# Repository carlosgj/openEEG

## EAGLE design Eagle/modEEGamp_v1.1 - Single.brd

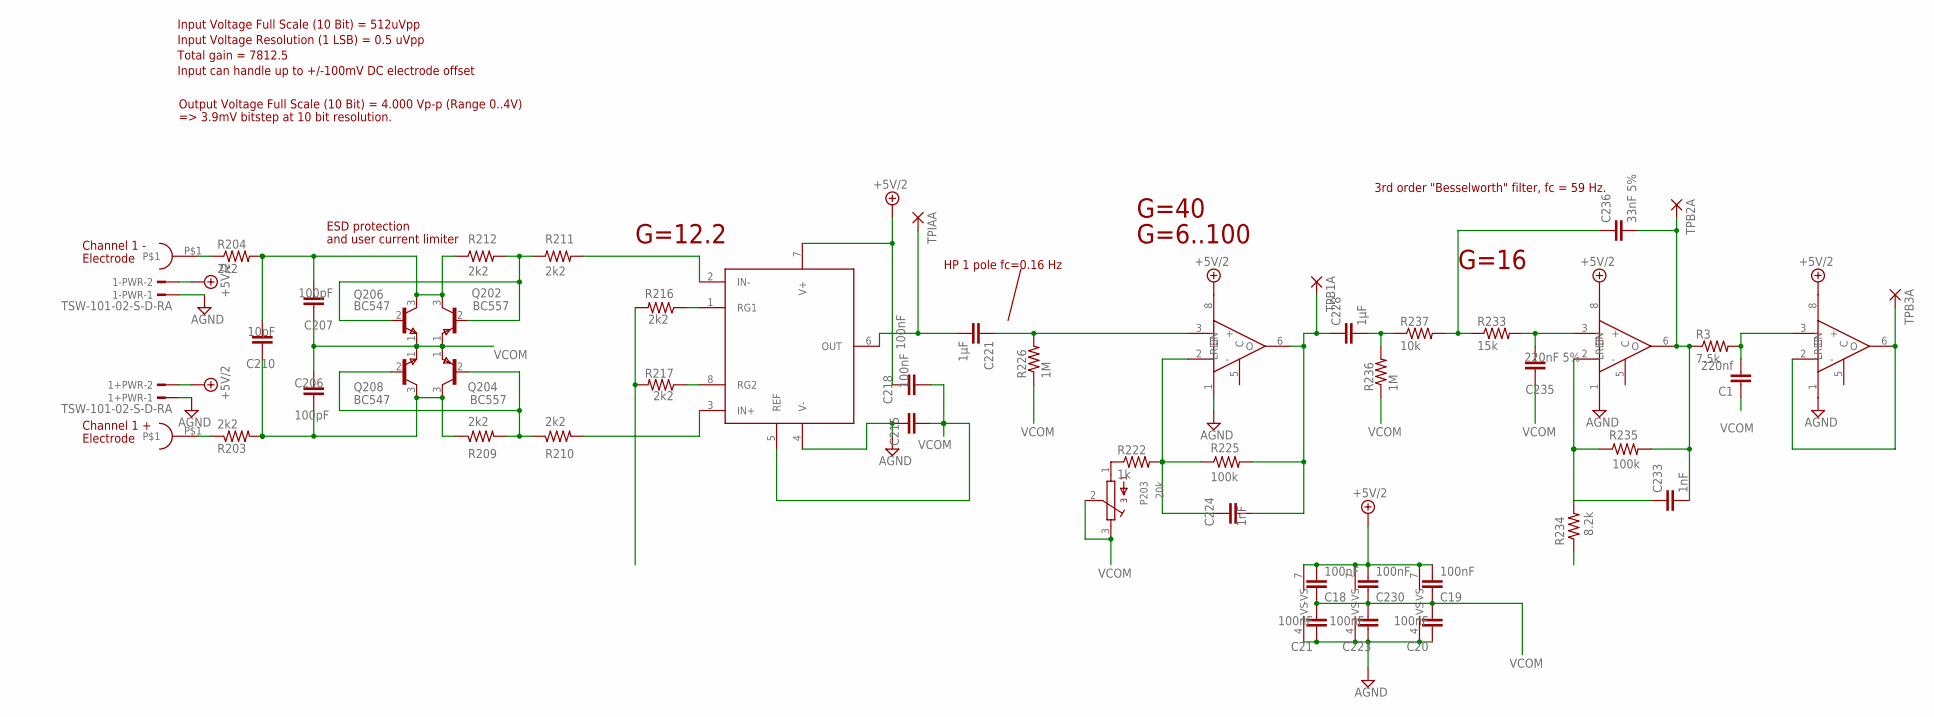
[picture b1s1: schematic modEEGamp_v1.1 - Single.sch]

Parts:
1+PWR, 1-PWR: TSW-101-02-S-D-RA
C1: 220nf; C1206
C1+, C1-: DIN42802
C18, C19, C20, C21, C215, C218, C223, C230: 100nF; C1206
C206, C207: 100pF; C1206
C210: 10pF; C1206
C221, C228: 1µF; C050-024X044
C224, C233: 1nF; C1206
C235: 220nF 5%; C1206
C236: 33nF 5%; C1206
P203: 20k; S64Y
Q202, Q204: BC557; TO92
Q206, Q208: BC547; TO92
R3: 7.5k; R1206
R203, R204, R209, R210, R211, R212, R216, R217: 2k2; R1206
R222: 1k; R1206
R225, R235: 100k; R1206
R226, R236: 1M; R1206
R233: 15k; R1206
R234: 8.2k; R1206
R237: 10k; R1206
TPB1A, TPB2A, TPB3A: 1,6/0,8
TPIAA: 1,6/0,8
U$1: INA217; DIL-08
U$2, U$3, U$16: AD8021; SOIC8

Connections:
+5V/2: 1+PWR.2, 1-PWR.2, C18.2, C19.2, C218.1, C230.2, U$1.7 (V+), U$2.7 (+VS), U$2.8 (EN), U$3.7 (+VS), U$3.8 (EN), U$16.7 (+VS), U$16.8 (EN)
ADIN0: TPB3A.1, U$16.2 (-), U$16.6 (O)
AGND: 1+PWR.1, 1-PWR.1, C20.1, C21.1, C215.1, C223.1, U$1.4 (V-), U$2.1 (LREF), U$2.4 (-VS), U$3.1 (LREF), U$3.4 (-VS), U$16.1 (LREF), U$16.4 (-VS)
unnamed: R216.1, U$1.1 (RG1)
unnamed: R217.1, U$1.8 (RG2)
unnamed: C233.2, C236.2, R3.1, R235.2, TPB2A.1, U$3.6 (O)
unnamed: C1-.P$1, R204.1
unnamed: C1.2, R3.2, U$16.3 (+)
unnamed: C1+.P$1, R203.1
unnamed: R216.2, R217.2
unnamed: R211.2, U$1.2 (IN-)
unnamed: C221.2, TPIAA.1, U$1.6 (OUT)
unnamed: R210.2, U$1.3 (IN+)
unnamed: C221.1, R226.2, U$2.3 (+)
unnamed: Q202.2 (B), Q206.2 (B), R211.1, R212.2
unnamed: C207.2, C210.2, Q202.3 (C), Q206.3 (C), R204.2, R212.1
unnamed: C224.1, R222.2, R225.1, U$2.2 (-)
unnamed: Q204.2 (B), Q208.2 (B), R209.2, R210.1
unnamed: P203.1, R222.1
unnamed: C224.2, C228.1, R225.2, TPB1A.1, U$2.6 (O)
unnamed: C206.1, C210.1, Q204.3 (C), Q208.3 (C), R203.2, R209.1
unnamed: C233.1, R234.2, R235.1, U$3.2 (-)
unnamed: C228.2, R236.2, R237.1
unnamed: C236.1, R233.1, R237.2
unnamed: C235.2, R233.2, U$3.3 (+)
VCOM: C1.1, C18.1, C19.1, C20.2, C21.2, C206.2, C207.1, C215.2, C218.2, C223.2, C230.1, C235.1, P203.2, P203.3, Q202.1 (E), Q204.1 (E), Q206.1 (E), Q208.1 (E), R226.1, R234.1, R236.1, U$1.5 (REF)

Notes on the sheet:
Electrode
Channel 1 -
Channel 1 +
Output Voltage Full Scale (10 Bit) = 4.000 Vp-p (Range 0..4V)
HP 1 pole fc=0.16 Hz
ESD protection
and user current limiter
G=12.2
G=16
G=40
G=6..100
Total gain = 7812.5
Input Voltage Resolution (1 LSB) = 0.5 uVpp
Input Voltage Full Scale (10 Bit) = 512uVpp
Input can handle up to +/-100mV DC electrode offset
3rd order "Besselworth" filter, fc = 59 Hz.
=> 3.9mV bitstep at 10 bit resolution.

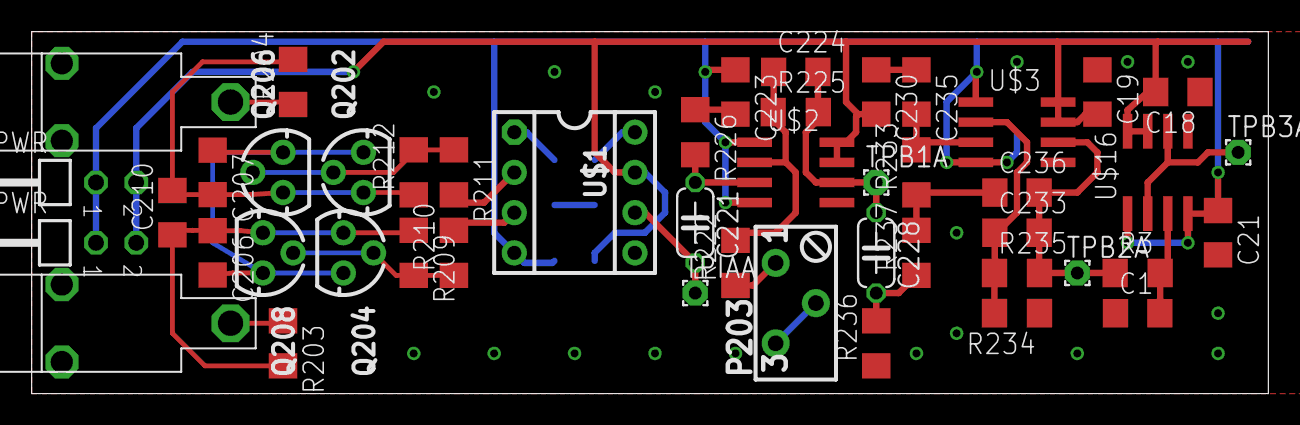
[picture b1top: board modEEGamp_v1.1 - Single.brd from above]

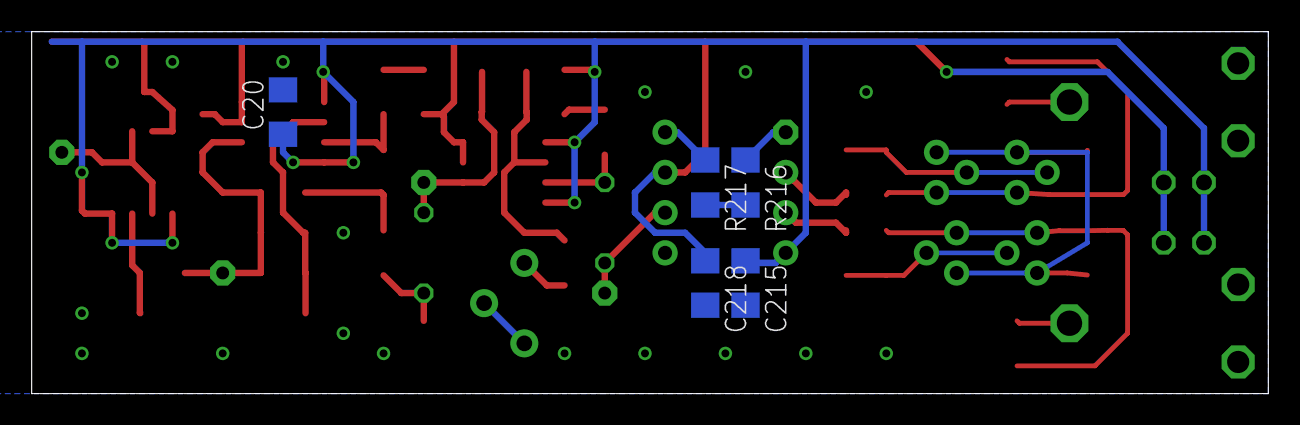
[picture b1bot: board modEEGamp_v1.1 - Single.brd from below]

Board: 2 copper layers, 78.1 x 22.9 mm, 52 parts (5 on the bottom side), 26 nets.

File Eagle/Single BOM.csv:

"Qty";"Value";"Device";"Package";"Parts";"Description";"";
"4";" ";"1,6/0,8";"1,6/0,8";"TPB1A, TPB2A, TPB3A, TPIAA";"THROUGH-HOLE PAD";"";
"2";"100k";"R-US_R1206";"R1206";"R225, R235";"RESISTOR, American symbol";"";
"8";"100nF";"C-EUC1206";"C1206";"C18, C19, C20, C21, C215, C218, C223, C230";"CAPACITOR, European symbol";"";
"2";"100pF";"C-EUC1206";"C1206";"C206, C207";"CAPACITOR, European symbol";"";
"1";"10k";"R-US_R1206";"R1206";"R237";"RESISTOR, American symbol";"";
"1";"10pF";"C-EUC1206";"C1206";"C210";"CAPACITOR, European symbol";"";
"1";"15k";"R-US_R1206";"R1206";"R233";"RESISTOR, American symbol";"";
"2";"1M";"R-US_R1206";"R1206";"R226, R236";"RESISTOR, American symbol";"";
"1";"1k";"R-US_R1206";"R1206";"R222";"RESISTOR, American symbol";"";
"2";"1nF";"C-EUC1206";"C1206";"C224, C233";"CAPACITOR, European symbol";"";
"2";"1µF";"C-EU050-024X044";"C050-024X044";"C221, C228";"CAPACITOR, European symbol";"";
"1";"20k";"S64Y";"S64Y";"P203";"";"";
"1";"220nF 5%";"C-EUC1206";"C1206";"C235";"CAPACITOR, European symbol";"";
"1";"220nf";"C-EUC1206";"C1206";"C1";"CAPACITOR, European symbol";"";
"8";"2k2";"R-US_R1206";"R1206";"R203, R204, R209, R210, R211, R212, R216, R217";"RESISTOR, American symbol";"";
"1";"33nF 5%";"C-EUC1206";"C1206";"C236";"CAPACITOR, European symbol";"";
"1";"7.5k";"R-US_R1206";"R1206";"R3";"RESISTOR, American symbol";"";
"1";"8.2k";"R-US_R1206";"R1206";"R234";"RESISTOR, American symbol";"";
"3";"AD8021";"AD8021";"SOIC8";"U$2, U$3, U$16";"";"";
"2";"BC547";"BC547";"TO92";"Q206, Q208";"";"";
"2";"BC557";"BC557";"TO92";"Q202, Q204";"";"";
"2";"DIN42802";"DIN42802";"DIN42802";"C1+, C1-";"";"";
"1";"INA217DW";"INA217DW";"DW_RPDSO-G16";"IC2";"Low-Noise, Low-Distortion INSTRUMENTATION AMPLIFIER Replacement for SSM2017";"";
"2";"TSW-101-02-S-D-RA";"TSW-101-02-S-D-RA";"TSW-101-02-S-D-RA";"1+PWR, 1-PWR";"THROUGH-HOLE .025" SQ POST HEADER";"";

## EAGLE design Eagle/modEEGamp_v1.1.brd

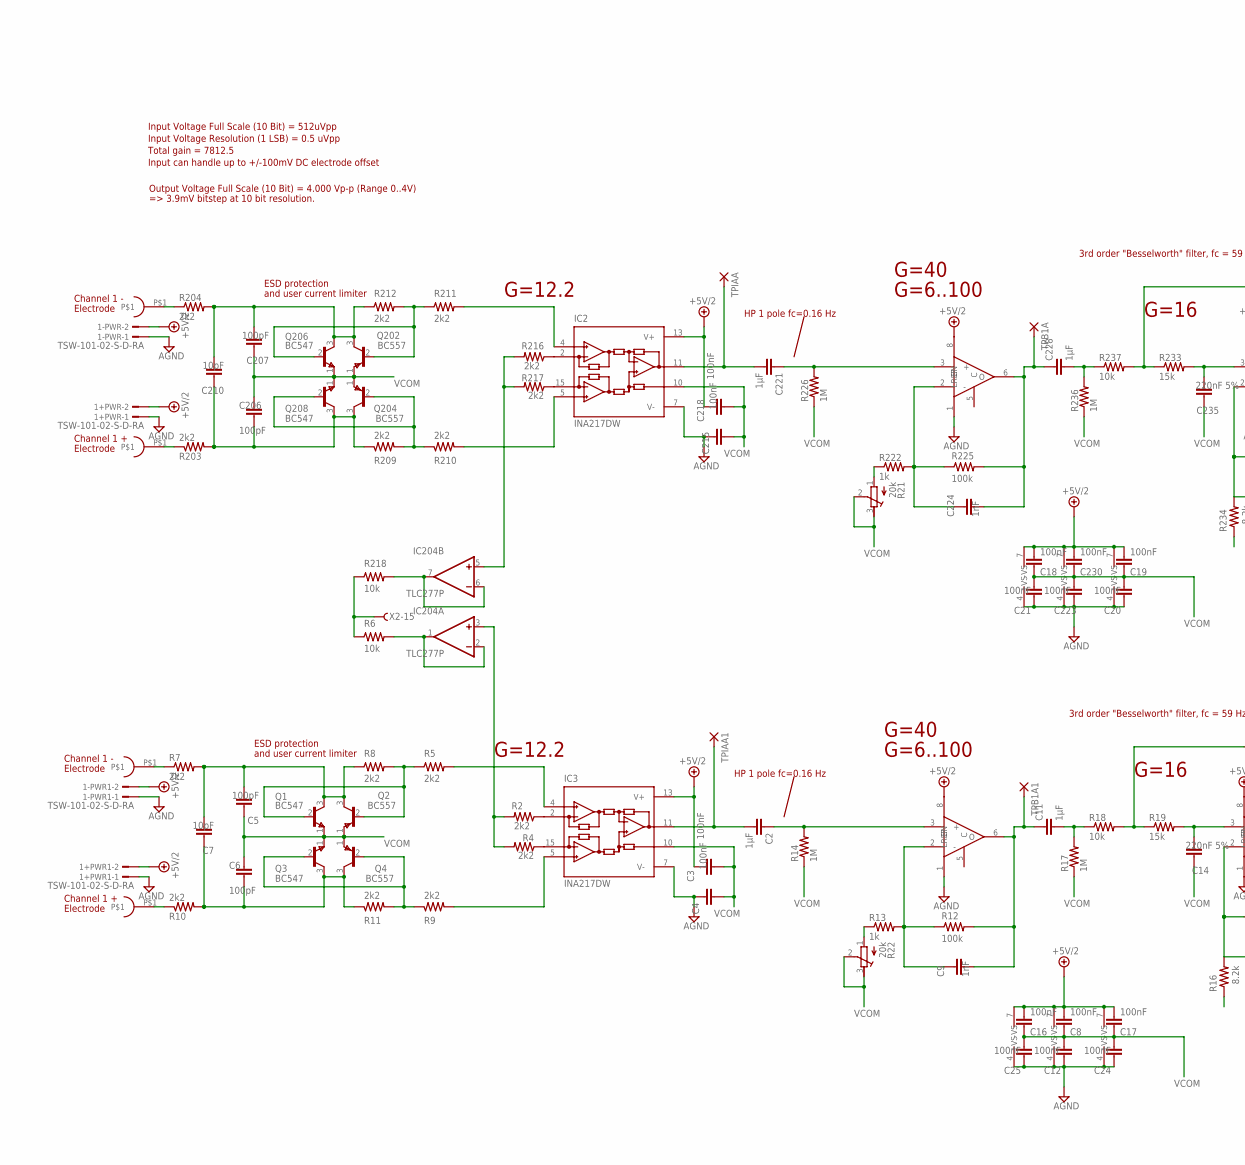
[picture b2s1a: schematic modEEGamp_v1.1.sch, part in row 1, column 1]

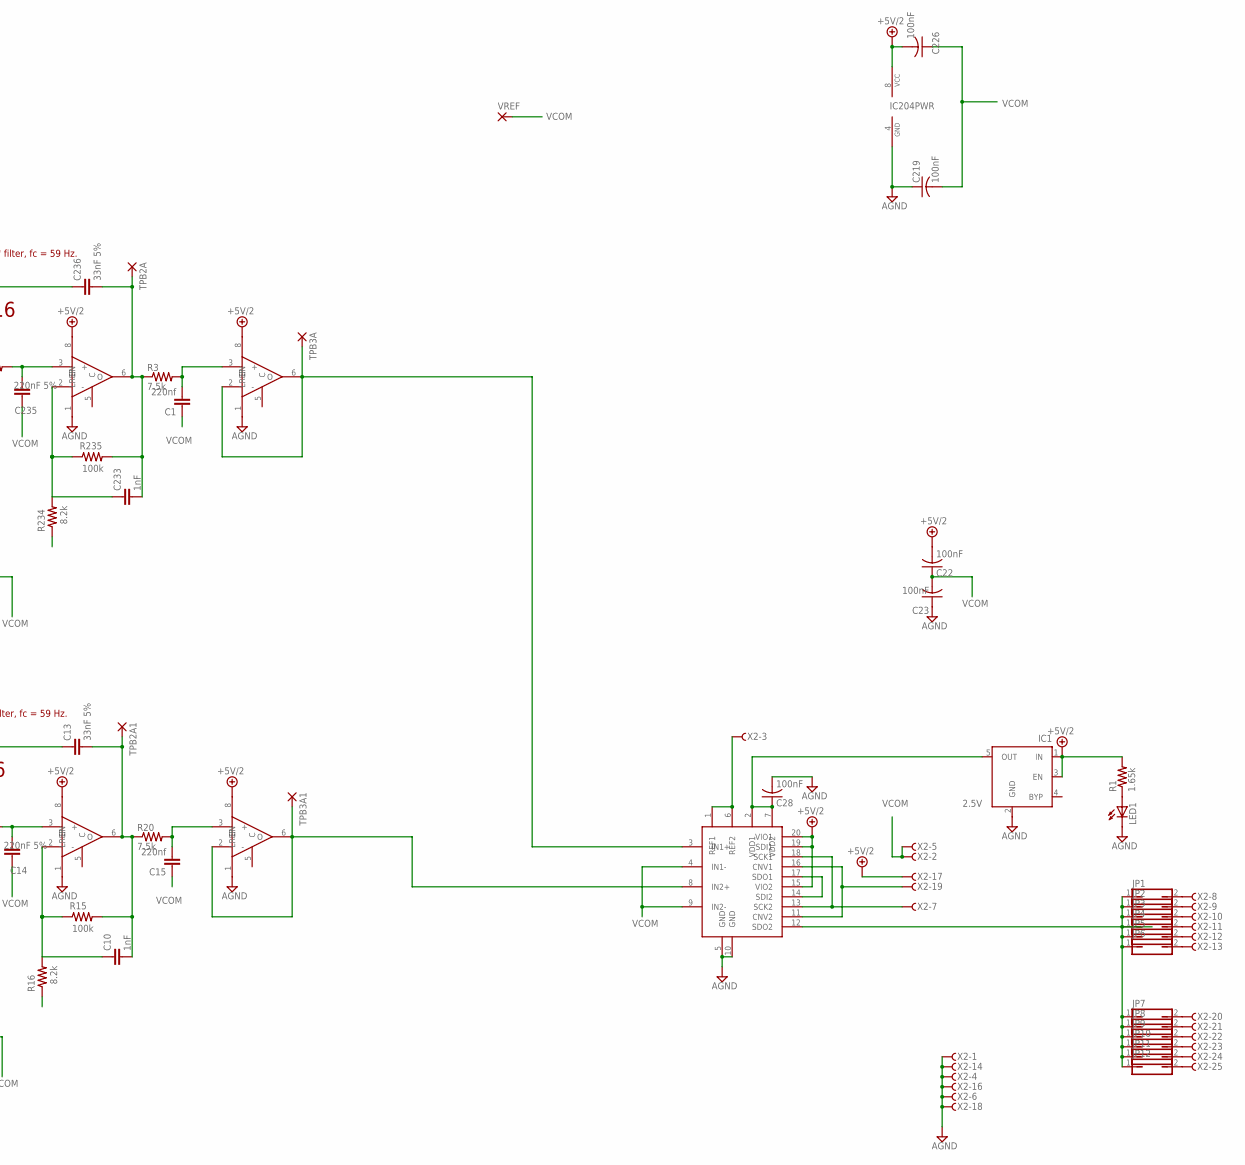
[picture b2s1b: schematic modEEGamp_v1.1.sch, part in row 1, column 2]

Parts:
1+PWR, 1+PWR1, 1-PWR, 1-PWR1: TSW-101-02-S-D-RA
C1, C15: 220nf; C1206
C1+, C1+1, C1-, C1-1: DIN42802
C2, C11, C221, C228: 1µF; C050-024X044
C3, C4, C8, C12, C16, C17, C18, C19, C20, C21, C22, C23, C24, C25, C28, C215, C218, C219, C223, C226, C230: 100nF; C1206
C5, C6, C206, C207: 100pF; C1206
C7, C210: 10pF; C1206
C9, C10, C224, C233: 1nF; C1206
C13, C236: 33nF 5%; C1206
C14, C235: 220nF 5%; C1206
IC1: 2.5V; SOT23-5
IC2, IC3: INA217DW; DW_RPDSO-G16
IC204: TLC277P; DIL-08
JP1, JP2, JP3, JP4, JP5, JP6, JP7, JP8, JP9, JP10, JP11, JP12: JP1Q; JP1
LED1: LED3MM
Q1, Q3, Q206, Q208: BC547; TO92
Q2, Q4, Q202, Q204: BC557; TO92
R1: 1.65k; R1206
R2, R4, R5, R7, R8, R9, R10, R11, R203, R204, R209, R210, R211, R212, R216, R217: 2k2; R1206
R3, R20: 7.5k; R1206
R6, R18, R218, R237: 10k; R1206
R12, R15, R225, R235: 100k; R1206
R13, R222: 1k; R1206
R14, R17, R226, R236: 1M; R1206
R16, R234: 8.2k; R1206
R19, R233: 15k; R1206
R21, R22: 20k; RTRIM3296W
TPB1A, TPB1A1, TPB2A, TPB2A1, TPB3A, TPB3A1: 1,6/0,8
TPIAA, TPIAA1: 1,6/0,8
U$1: AD7902; QSOP20
U$10, U$12, U$20, U$30, U$31, U$36: AD8021; SOIC8
VREF: 1,6/0,8
X2: F25HPS; F25HP

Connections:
+5V/2: 1+PWR.2, 1+PWR1.2, 1-PWR.2, 1-PWR1.2, C3.1, C8.2, C16.2, C17.2, C18.2, C19.2, C22.2, C218.1, C226.2, C230.2, IC1.1 (IN), IC1.3 (EN), IC2.13 (V+), IC3.13 (V+), IC204.8 (VCC), R1.2, U$1.15 (VIO2), U$1.19 (SDI1), U$1.20 (VIO1), U$10.7 (+VS), U$10.8 (EN), U$12.7 (+VS), U$12.8 (EN), U$20.7 (+VS), U$20.8 (EN), U$30.7 (+VS), U$30.8 (EN), U$31.7 (+VS), U$31.8 (EN), U$36.7 (+VS), U$36.8 (EN), X2.17
ADIN0: TPB3A.1, U$1.3 (IN1+), U$20.2 (-), U$20.6 (O)
ADIN1: TPB3A1.1, U$1.8 (IN2+), U$36.2 (-), U$36.6 (O)
AGND: 1+PWR.1, 1+PWR1.1, 1-PWR.1, 1-PWR1.1, C4.1, C12.1, C20.1, C21.1, C23.1, C24.1, C25.1, C28.2, C215.1, C219.1, C223.1, IC1.2 (GND), IC2.7 (V-), IC3.7 (V-), IC204.4 (GND), LED1.K (C), U$1.5 (GND), U$1.10 (GND), U$10.1 (LREF), U$10.4 (-VS), U$12.1 (LREF), U$12.4 (-VS), U$20.1 (LREF), U$20.4 (-VS), U$30.1 (LREF), U$30.4 (-VS), U$31.1 (LREF), U$31.4 (-VS), U$36.1 (LREF), U$36.4 (-VS), X2.1, X2.4, X2.6, X2.14, X2.16, X2.18
CNV: U$1.11 (CNV2), U$1.16 (CNV1), X2.19
unnamed: U$1.1 (REF1), U$1.6 (REF2), X2.3
unnamed: C28.1, IC1.5 (OUT), U$1.2 (VDD1), U$1.7 (VDD2)
unnamed: JP1.1, JP2.1, JP3.1, JP4.1, JP5.1, JP6.1, JP7.1, JP8.1, JP9.1, JP10.1, JP11.1, JP12.1, U$1.12 (SDO2)
unnamed: U$1.14 (SDI2), U$1.17 (SDO1)
unnamed: C1-.P$1, R204.1
unnamed: R13.1, R22.1 (A)
unnamed: C1+.P$1, R203.1
unnamed: R21.1 (A), R222.1
unnamed: LED1.A, R1.1
unnamed: JP1.2, X2.8
unnamed: JP2.2, X2.9
unnamed: IC204.5 (+IN), R216.2, R217.2
unnamed: C233.2, C236.2, R3.1, R235.2, TPB2A.1, U$12.6 (O)
unnamed: IC2.2 (RG1), R216.1
unnamed: C1.2, R3.2, U$20.3 (+)
unnamed: IC204.3 (+IN), R2.2, R4.2
unnamed: C2.2, IC3.11 (OUT), TPIAA1.1
unnamed: IC3.4 (-IN), R5.2
unnamed: IC3.5 (+IN), R9.2
unnamed: IC2.15 (RG2), R217.1
unnamed: IC2.4 (-IN), R211.2
unnamed: Q1.2 (B), Q2.2 (B), R5.1, R8.2
unnamed: C5.2, C7.2, Q1.3 (C), Q2.3 (C), R7.2, R8.1
unnamed: Q3.2 (B), Q4.2 (B), R9.1, R11.2
unnamed: C221.2, IC2.11 (OUT), TPIAA.1
unnamed: C6.1, C7.1, Q3.3 (C), Q4.3 (C), R10.2, R11.1
unnamed: IC2.5 (+IN), R210.2
unnamed: C221.1, R226.2, U$10.3 (+)
unnamed: Q202.2 (B), Q206.2 (B), R211.1, R212.2
unnamed: C1-1.P$1, R7.1
unnamed: C1+1.P$1, R10.1
unnamed: C207.2, C210.2, Q202.3 (C), Q206.3 (C), R204.2, R212.1
unnamed: C2.1, R14.2, U$30.3 (+)
unnamed: C9.1, R12.1, R13.2, U$30.2 (-)
unnamed: IC204.1 (OUT), IC204.2 (-IN), R6.2
unnamed: JP3.2, X2.10
unnamed: C9.2, C11.1, R12.2, TPB1A1.1, U$30.6 (O)
unnamed: C224.1, R222.2, R225.1, U$10.2 (-)
unnamed: Q204.2 (B), Q208.2 (B), R209.2, R210.1
unnamed: JP4.2, X2.11
unnamed: C13.1, R18.2, R19.1
unnamed: C224.2, C228.1, R225.2, TPB1A.1, U$10.6 (O)
unnamed: C206.1, C210.1, Q204.3 (C), Q208.3 (C), R203.2, R209.1
unnamed: C14.2, R19.2, U$31.3 (+)
unnamed: C11.2, R17.2, R18.1
unnamed: C10.1, R15.1, R16.2, U$31.2 (-)
unnamed: IC3.2 (RG1), R2.1
unnamed: IC3.15 (RG2), R4.1
unnamed: C233.1, R234.2, R235.1, U$12.2 (-)
unnamed: C228.2, R236.2, R237.1
unnamed: C236.1, R233.1, R237.2
unnamed: IC204.6 (-IN), IC204.7 (OUT), R218.2
unnamed: C10.2, C13.2, R15.2, R20.1, TPB2A1.1, U$31.6 (O)
unnamed: C15.2, R20.2, U$36.3 (+)
unnamed: JP5.2, X2.12
unnamed: JP6.2, X2.13
unnamed: C235.2, R233.2, U$12.3 (+)
unnamed: JP7.2, X2.20
unnamed: JP8.2, X2.21
unnamed: JP9.2, X2.22
unnamed: JP10.2, X2.23
unnamed: JP11.2, X2.24
unnamed: JP12.2, X2.25
unnamed: R6.1, R218.1, X2.15
SCK: U$1.13 (SCK2), U$1.18 (SCK1), X2.7
VCOM: C1.1, C3.2, C4.2, C5.1, C6.2, C8.1, C12.2, C14.1, C15.1, C16.1, C17.1, C18.1, C19.1, C20.2, C21.2, C22.1, C23.2, C24.2, C25.2, C206.2, C207.1, C215.2, C218.2, C219.2, C223.2, C226.1, C230.1, C235.1, IC2.10 (REF), IC3.10 (REF), Q1.1 (E), Q2.1 (E), Q3.1 (E), Q4.1 (E), Q202.1 (E), Q204.1 (E), Q206.1 (E), Q208.1 (E), R14.1, R16.1, R17.1, R21.2 (S), R21.3 (E), R22.2 (S), R22.3 (E), R226.1, R234.1, R236.1, U$1.4 (IN1-), U$1.9 (IN2-), VREF.1, X2.2, X2.5

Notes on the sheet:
Electrode
Channel 1 -
Channel 1 +
Output Voltage Full Scale (10 Bit) = 4.000 Vp-p (Range 0..4V)
HP 1 pole fc=0.16 Hz
ESD protection
and user current limiter
G=12.2
G=16
G=40
G=6..100
Total gain = 7812.5
Input Voltage Resolution (1 LSB) = 0.5 uVpp
Input Voltage Full Scale (10 Bit) = 512uVpp
Input can handle up to +/-100mV DC electrode offset
3rd order "Besselworth" filter, fc = 59 Hz.
=> 3.9mV bitstep at 10 bit resolution.

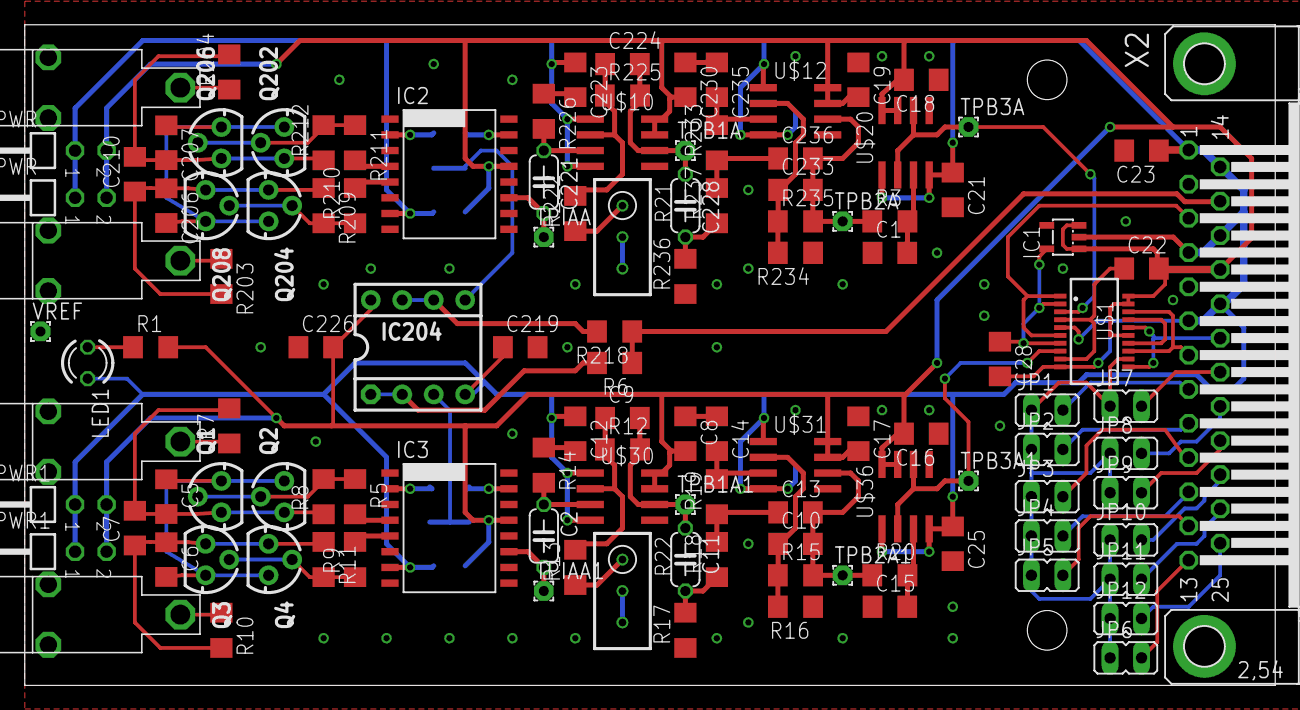
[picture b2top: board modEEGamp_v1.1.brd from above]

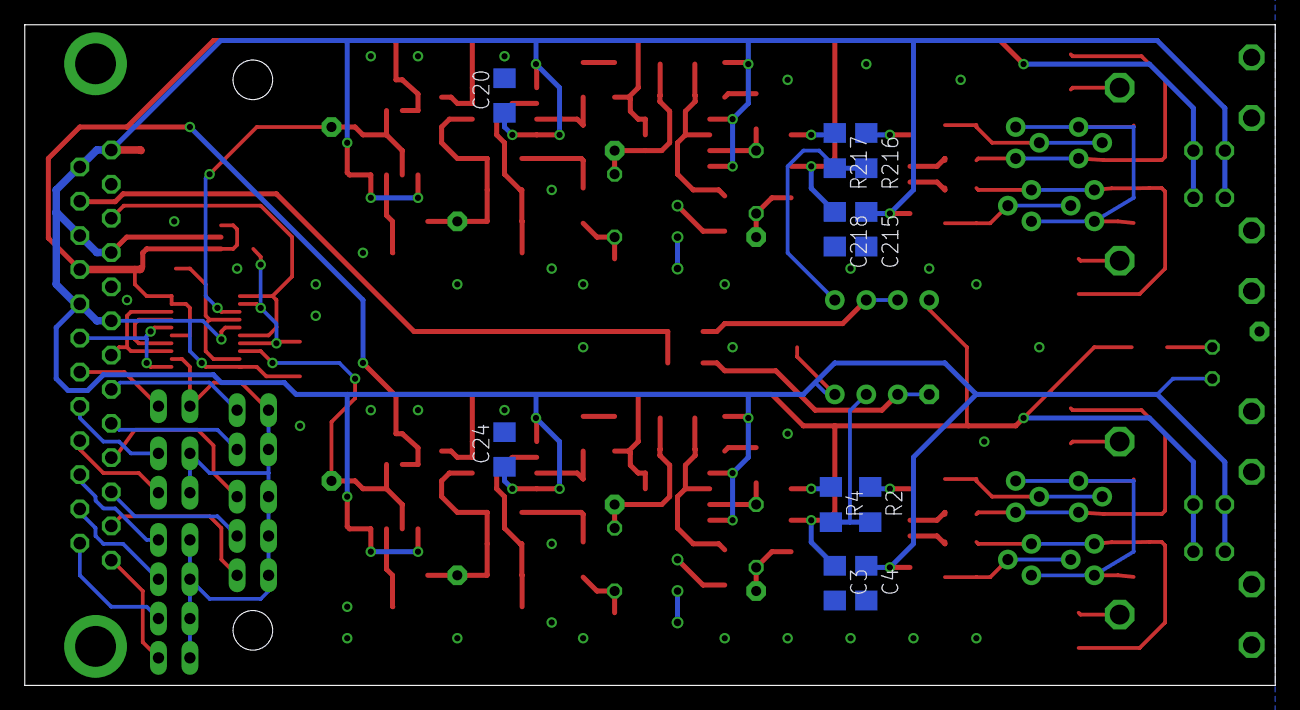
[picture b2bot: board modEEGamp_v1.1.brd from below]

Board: 2 copper layers, 101.0 x 53.3 mm, 130 parts (10 on the bottom side), 71 nets.

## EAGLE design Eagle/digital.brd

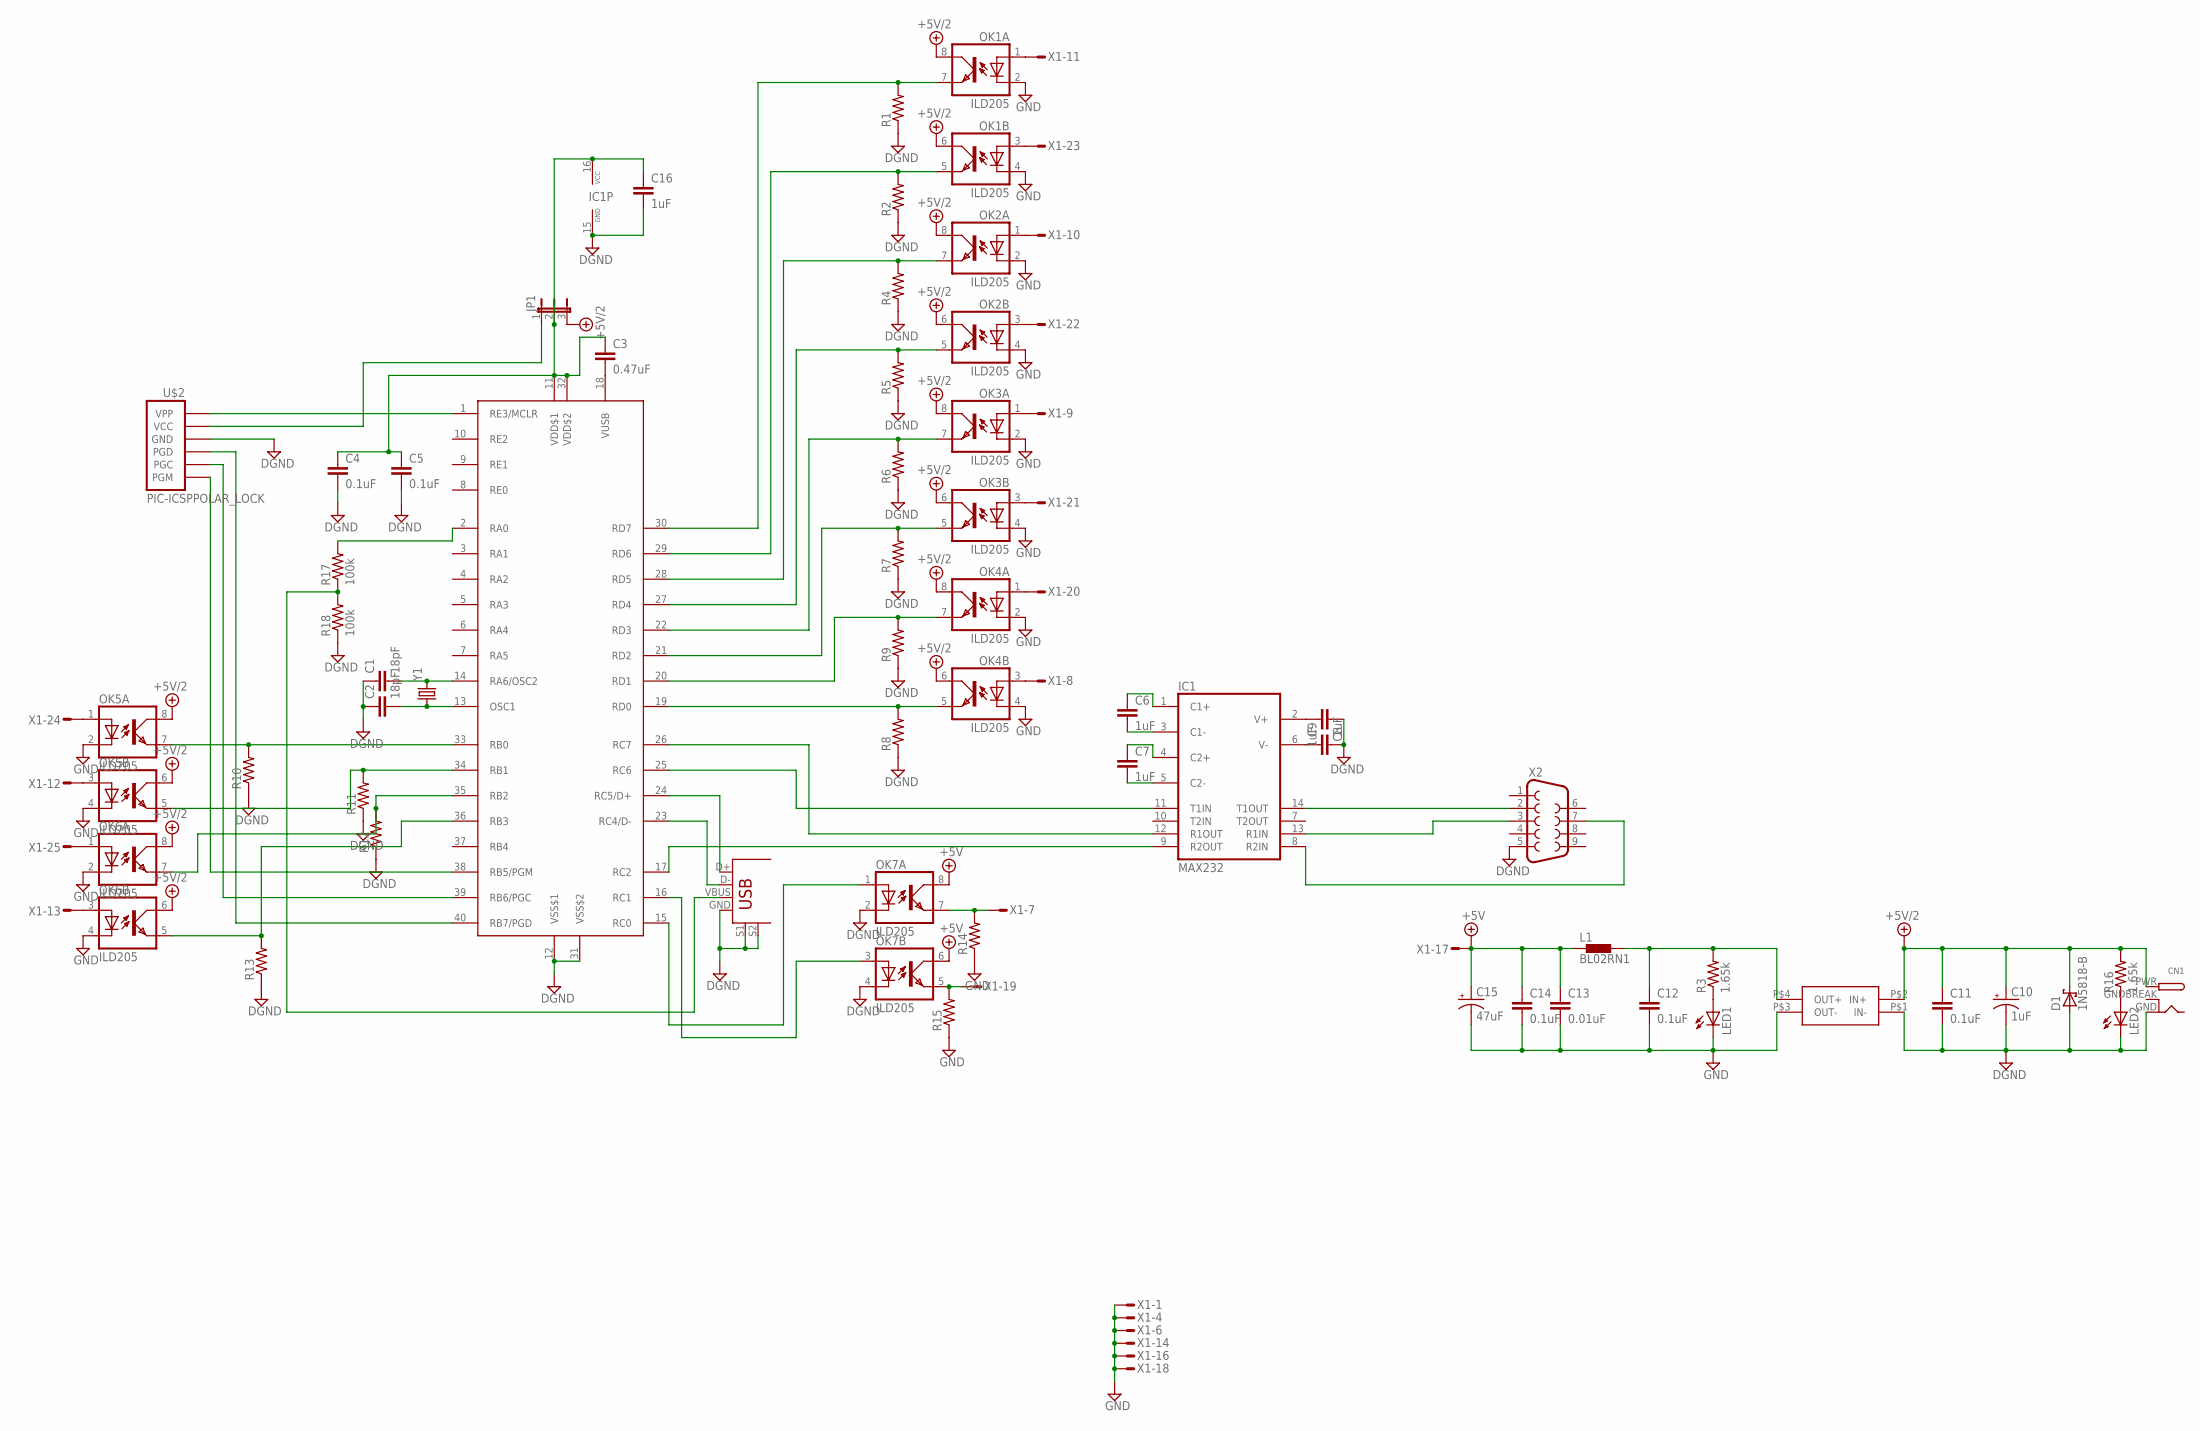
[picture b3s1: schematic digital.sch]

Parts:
C1, C2: 18pF; C050-025X075
C3: 0.47uF; C050-025X075
C4, C5, C11, C12, C14: 0.1uF; C050-025X075
C6, C7, C8, C9, C16: 1uF; C050-025X075
C10: 1uF; E5-8,5
C13: 0.01uF; C050-025X075
C15: 47uF; E5-8,5
CN1: DCBARRELPTH; DCJACK_2MM_PTH
D1: 1N5818-B; DO41-7.6
IC1: MAX232; DIL16
J1: USB+SHIELD; USB-B-PTH
JP1: JP2E; JP2
L1: BL02RN1
LED1, LED2: LED3MM
OK1, OK2, OK3, OK4, OK5, OK6, OK7: ILD205; SOIC08
R1, R2, R4, R5, R6, R7, R8, R9, R10, R11, R12, R13, R14, R15: R-US_0204/2V; 0204V
R3, R16: 1.65k; 0204V
R17, R18: 100k; 0204V
U$1: PIC18F4458; DIL40
U$2: PIC-ICSPPOLAR_LOCK; MOLEX-1X6_LOCK
U$3: ROL-0505S; SIP4
X1: M25HS; M25H
X2: F09HP
Y1: CRYSTALHC49US; HC49US

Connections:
+5V: C13.1, C14.1, C15.+, L1.1, OK7.6 (COL), OK7.8 (COL), X1.17
+5V/2: C10.+, C11.1, CN1.PWR, D1.C, JP1.3, OK1.6 (COL), OK1.8 (COL), OK2.6 (COL), OK2.8 (COL), OK3.6 (COL), OK3.8 (COL), OK4.6 (COL), OK4.8 (COL), OK5.6 (COL), OK5.8 (COL), OK6.6 (COL), OK6.8 (COL), R16.2, U$3.P$2 (IN+)
DGND: C1.1, C2.1, C4.2, C5.2, C8.1, C9.2, C10.-, C11.2, C16.2, CN1.GND, D1.A, IC1.15 (GND), J1.GND, J1.S1, J1.S2, LED2.K (C), OK7.2 (C), OK7.4 (C), R1.1, R2.1, R4.1, R5.1, R6.1, R7.1, R8.1, R9.1, R10.1, R11.1, R12.1, R13.1, R18.1, U$1.12 (VSS$1), U$1.31 (VSS$2), U$2.4 (GND), U$3.P$1 (IN-), X2.5
GND: C12.2, C13.2, C14.2, C15.-, LED1.K (C), OK1.2 (C), OK1.4 (C), OK2.2 (C), OK2.4 (C), OK3.2 (C), OK3.4 (C), OK4.2 (C), OK4.4 (C), OK5.2 (C), OK5.4 (C), OK6.2 (C), OK6.4 (C), R14.1, R15.1, U$3.P$3 (OUT-), X1.1, X1.4, X1.6, X1.14, X1.16, X1.18
GNDBREAK: CN1.GNDBREAK
unnamed: C1.2, U$1.14 (RA6/OSC2), Y1.2
unnamed: C2.2, U$1.13 (OSC1), Y1.1
unnamed: IC1.8 (R2IN), X2.7
unnamed: IC1.9 (R2OUT), U$1.17 (RC2)
unnamed: U$1.1 (RE3/MCLR), U$2.6 (VPP)
unnamed: U$1.38 (RB5/PGM), U$2.1 (PGM)
unnamed: U$1.39 (RB6/PGC), U$2.2 (PGC)
unnamed: U$1.40 (RB7/PGD), U$2.3 (PGD)
unnamed: C3.2, U$1.18 (VUSB)
unnamed: JP1.1, U$2.5 (VCC)
unnamed: OK1.1 (A), X1.11
unnamed: OK1.3 (A), X1.23
unnamed: OK2.1 (A), X1.10
unnamed: OK2.3 (A), X1.22
unnamed: OK1.7 (EMIT), R1.2, U$1.30 (RD7)
unnamed: OK3.1 (A), X1.9
unnamed: OK3.3 (A), X1.21
unnamed: OK4.1 (A), X1.20
unnamed: OK4.3 (A), X1.8
unnamed: OK5.1 (A), X1.24
unnamed: OK5.3 (A), X1.12
unnamed: OK6.1 (A), X1.25
unnamed: OK6.3 (A), X1.13
unnamed: OK1.5 (EMIT), R2.2, U$1.29 (RD6)
unnamed: OK2.7 (EMIT), R4.2, U$1.28 (RD5)
unnamed: C12.1, L1.2, R3.2, U$3.P$4 (OUT+)
unnamed: OK2.5 (EMIT), R5.2, U$1.27 (RD4)
unnamed: LED1.A, R3.1
unnamed: OK3.7 (EMIT), R6.2, U$1.22 (RD3)
unnamed: OK3.5 (EMIT), R7.2, U$1.21 (RD2)
unnamed: OK4.7 (EMIT), R9.2, U$1.20 (RD1)
unnamed: OK4.5 (EMIT), R8.2, U$1.19 (RD0)
unnamed: OK5.7 (EMIT), R10.2, U$1.33 (RB0)
unnamed: OK5.5 (EMIT), R11.2, U$1.34 (RB1)
unnamed: OK6.7 (EMIT), R12.2, U$1.35 (RB2)
unnamed: OK6.5 (EMIT), R13.2, U$1.36 (RB3)
unnamed: OK7.7 (EMIT), R14.2, X1.7
unnamed: OK7.5 (EMIT), R15.2, X1.19
unnamed: OK7.1 (A), U$1.15 (RC0)
unnamed: OK7.3 (A), U$1.16 (RC1)
unnamed: LED2.A, R16.1
unnamed: J1.VBUS, R17.1, R18.2
unnamed: IC1.11 (T1IN), U$1.25 (RC6)
unnamed: C3.1, C4.1, C5.1, C16.1, IC1.16 (VCC), JP1.2, U$1.11 (VDD$1), U$1.32 (VDD$2)
unnamed: IC1.12 (R1OUT), U$1.26 (RC7)
unnamed: C8.2, IC1.2 (V+)
unnamed: C9.1, IC1.6 (V-)
unnamed: C6.2, IC1.3 (C1-)
unnamed: C6.1, IC1.1 (C1+)
unnamed: C7.1, IC1.4 (C2+)
unnamed: C7.2, IC1.5 (C2-)
unnamed: IC1.13 (R1IN), X2.3
unnamed: IC1.14 (T1OUT), X2.2
unnamed: R17.2, U$1.2 (RA0)
USB_N: J1.D-, U$1.23 (RC4/D-)
USB_P: J1.D+, U$1.24 (RC5/D+)

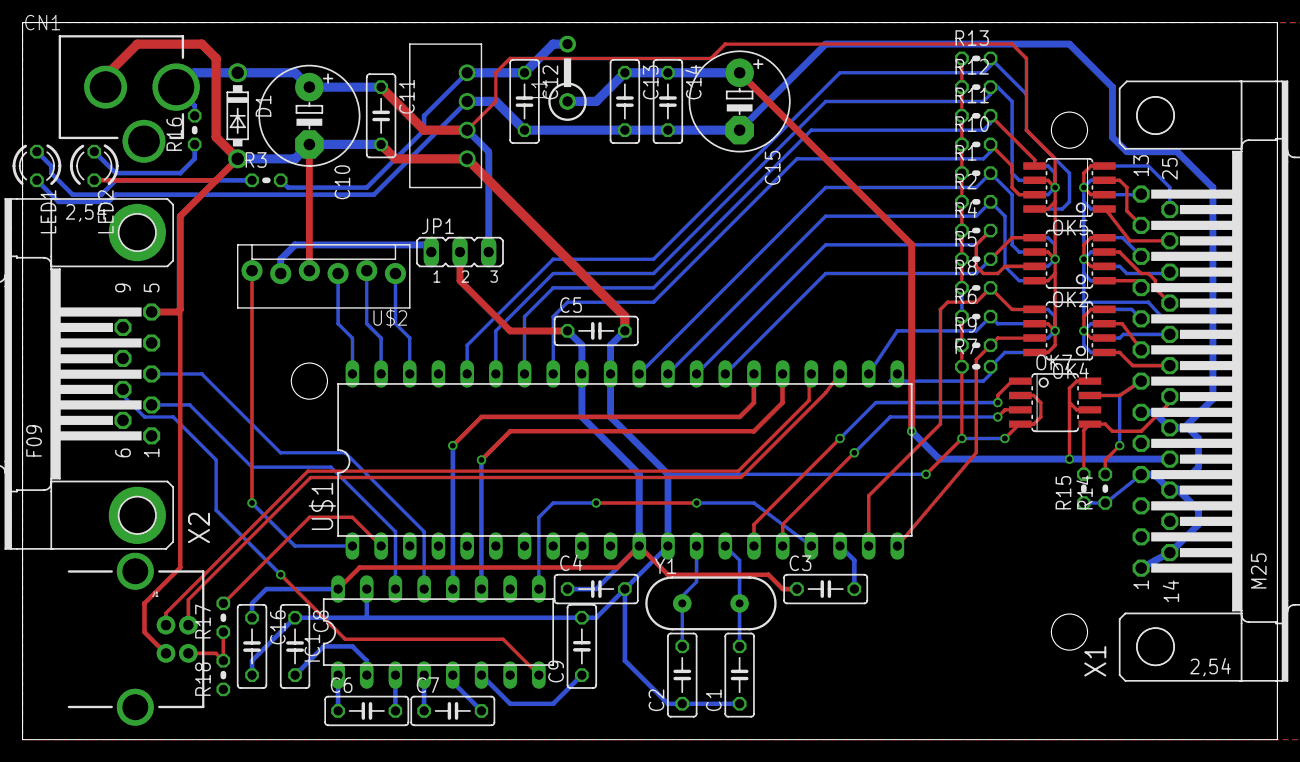
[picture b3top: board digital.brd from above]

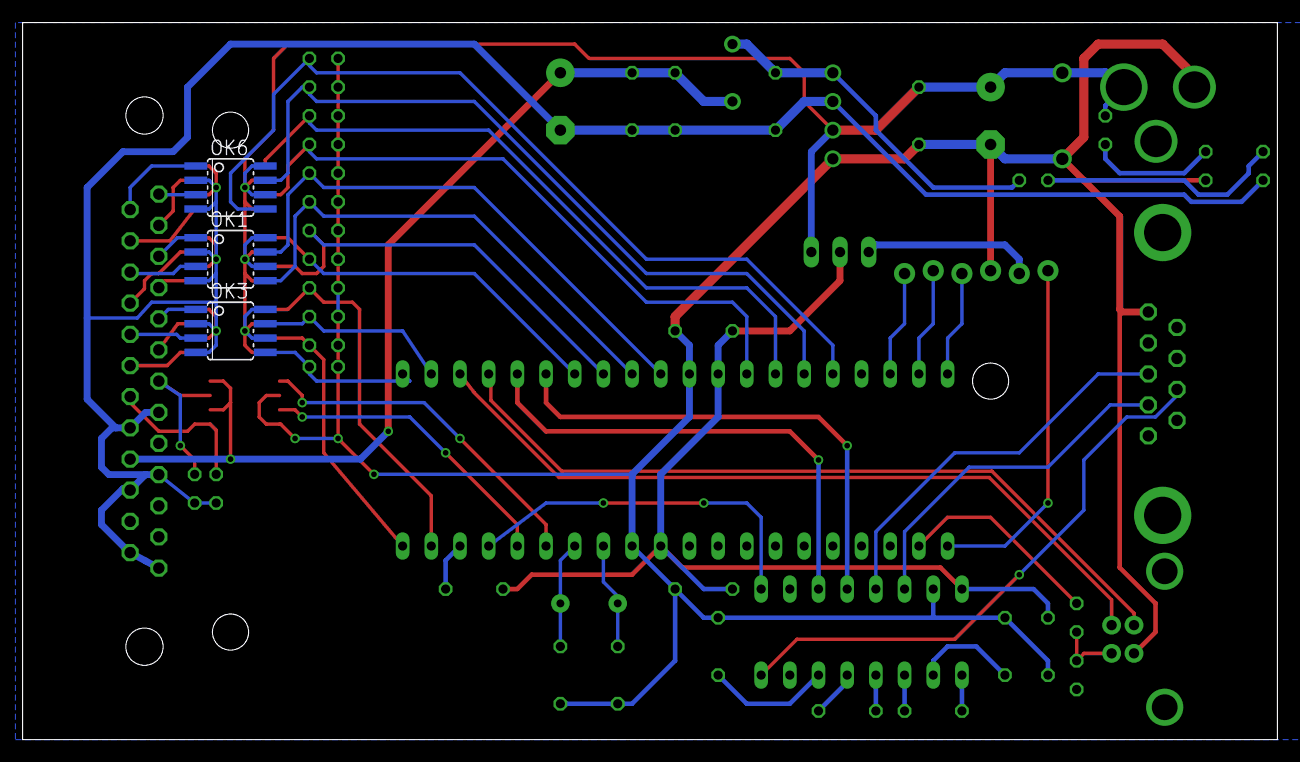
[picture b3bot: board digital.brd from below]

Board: 2 copper layers, 111.1 x 63.5 mm, 55 parts (3 on the bottom side), 60 nets.

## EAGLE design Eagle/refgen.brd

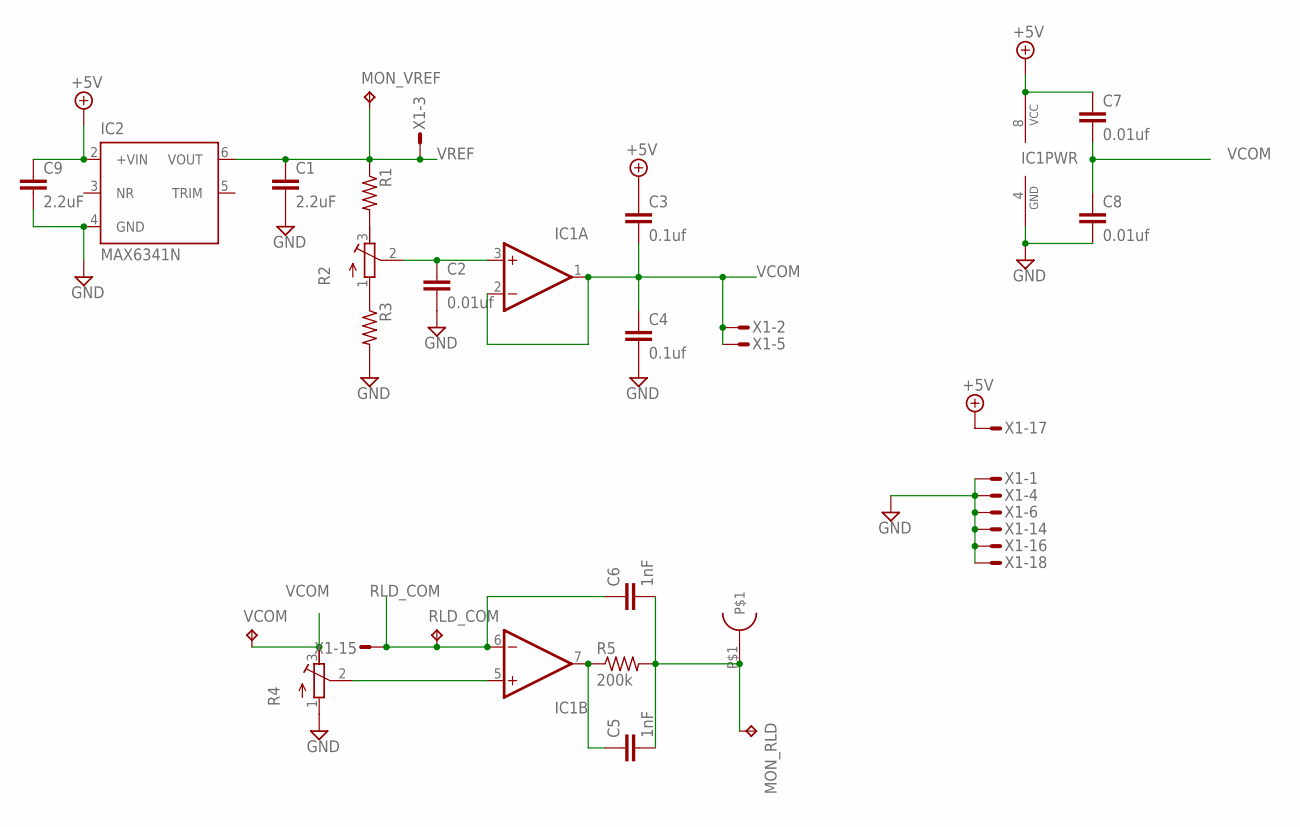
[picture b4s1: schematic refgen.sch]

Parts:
C1, C9: 2.2uF; C050-025X075
C2, C7, C8: 0.01uf; C050-025X075
C3, C4: 0.1uf; C050-025X075
C5, C6: 1nF; C050-025X075
IC1: TLC277P; DIL-08
IC2: MAX6341N; DIL08
MON_RLD: TPPAD1-17; P1-17
MON_VREF: TPPAD1-17; P1-17
R1, R3: R-US_0204/2V; 0204V
R2, R4: R-TRIMM3296W; RTRIM3296W
R5: 200k; 0204V
RLD_COM: TPPAD1-17; P1-17
RLD_OUT: DIN42802
VCOM: TPPAD1-17; P1-17
X1: M25HPS; M25HP

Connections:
+5V: C3.1, C7.1, C9.1, IC1.8 (VCC), IC2.2 (+VIN), X1.17
GND: C1.2, C2.2, C4.2, C8.2, C9.2, IC1.4 (GND), IC2.4 (GND), R3.2, R4.1 (A), X1.1, X1.4, X1.6, X1.14, X1.16, X1.18
unnamed: C5.1, IC1.7 (OUT), R5.1
unnamed: R1.2, R2.3 (E)
unnamed: R2.1 (A), R3.1
unnamed: C2.1, IC1.3 (+IN), R2.2 (S)
unnamed: C5.2, C6.2, MON_RLD.TP, R5.2, RLD_OUT.P$1
unnamed: IC1.5 (+IN), R4.2 (S)
RLD_COM: C6.1, IC1.6 (-IN), RLD_COM.TP, X1.15
VCOM: C3.2, C4.1, C7.2, C8.1, IC1.1 (OUT), IC1.2 (-IN), R4.3 (E), VCOM.TP, X1.2, X1.5
VREF: C1.1, IC2.6 (VOUT), MON_VREF.TP, R1.1, X1.3

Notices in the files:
parts and their libraries:
SparkFun-Connectors: Licensing: Creative Commons ShareAlike 4.0 International - https://creativecommons.org/licenses/by-sa/4.0
